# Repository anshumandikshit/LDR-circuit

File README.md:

# LDR-circuit
PCB design of LDR circuit

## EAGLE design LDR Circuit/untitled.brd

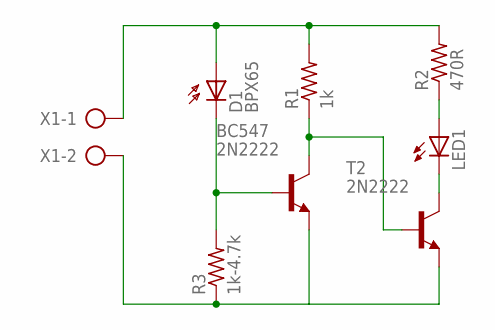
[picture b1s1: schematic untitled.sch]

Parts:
BC547: 2N2222; TO92-EBC-OVAL
D1: BPX65
LED1: LED3MM
R1: 1k; 0204/5
R2: 470R; 0204/5
R3: 1k-4.7k; 0204/5
T2: 2N2222; TO92-EBC-OVAL
X1: AK500/2

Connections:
unnamed: D1.A, R1.2, R2.2, X1.1
unnamed: BC547.B, D1.K (C), R3.2
unnamed: BC547.C, R1.1, T2.B
unnamed: BC547.E, R3.1, T2.E, X1.2
unnamed: LED1.A, R2.1
unnamed: LED1.K (C), T2.C

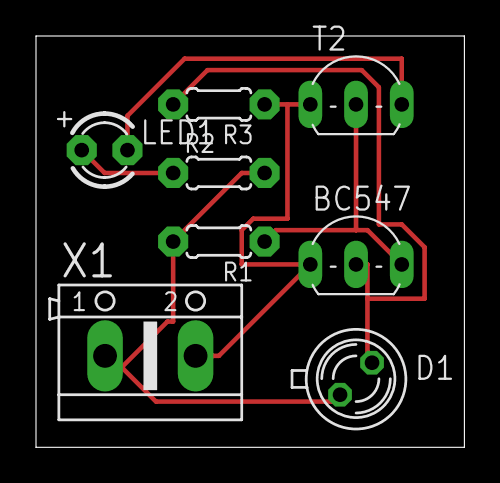
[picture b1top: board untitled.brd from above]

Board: 2 copper layers, 23.8 x 22.9 mm, 8 parts (0 on the bottom side), 6 nets.

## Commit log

2017-08-31 LDR circuit PCB
